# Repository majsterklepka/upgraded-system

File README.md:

# upgraded-system
Arduino Based Multi-channel Voltmeter

Arduino Design, multi-channel ADC.

- Application for OS Linux, works in terminal mode
- Sketch for Arduino UNO
- hardware project of shield for Arduino Uno

That's All! Have a fun!

## Credits

All contents on this repo is published under terms of: [CC-BY-SA](https://creativecommons.org/licenses/by-sa/4.0/) for hardware & [GNU GPLv3](https://www.gnu.org/licenses/gpl-3.0.html) for Linux software

_MSc Paweł Sobótka (SQ7EQE)_

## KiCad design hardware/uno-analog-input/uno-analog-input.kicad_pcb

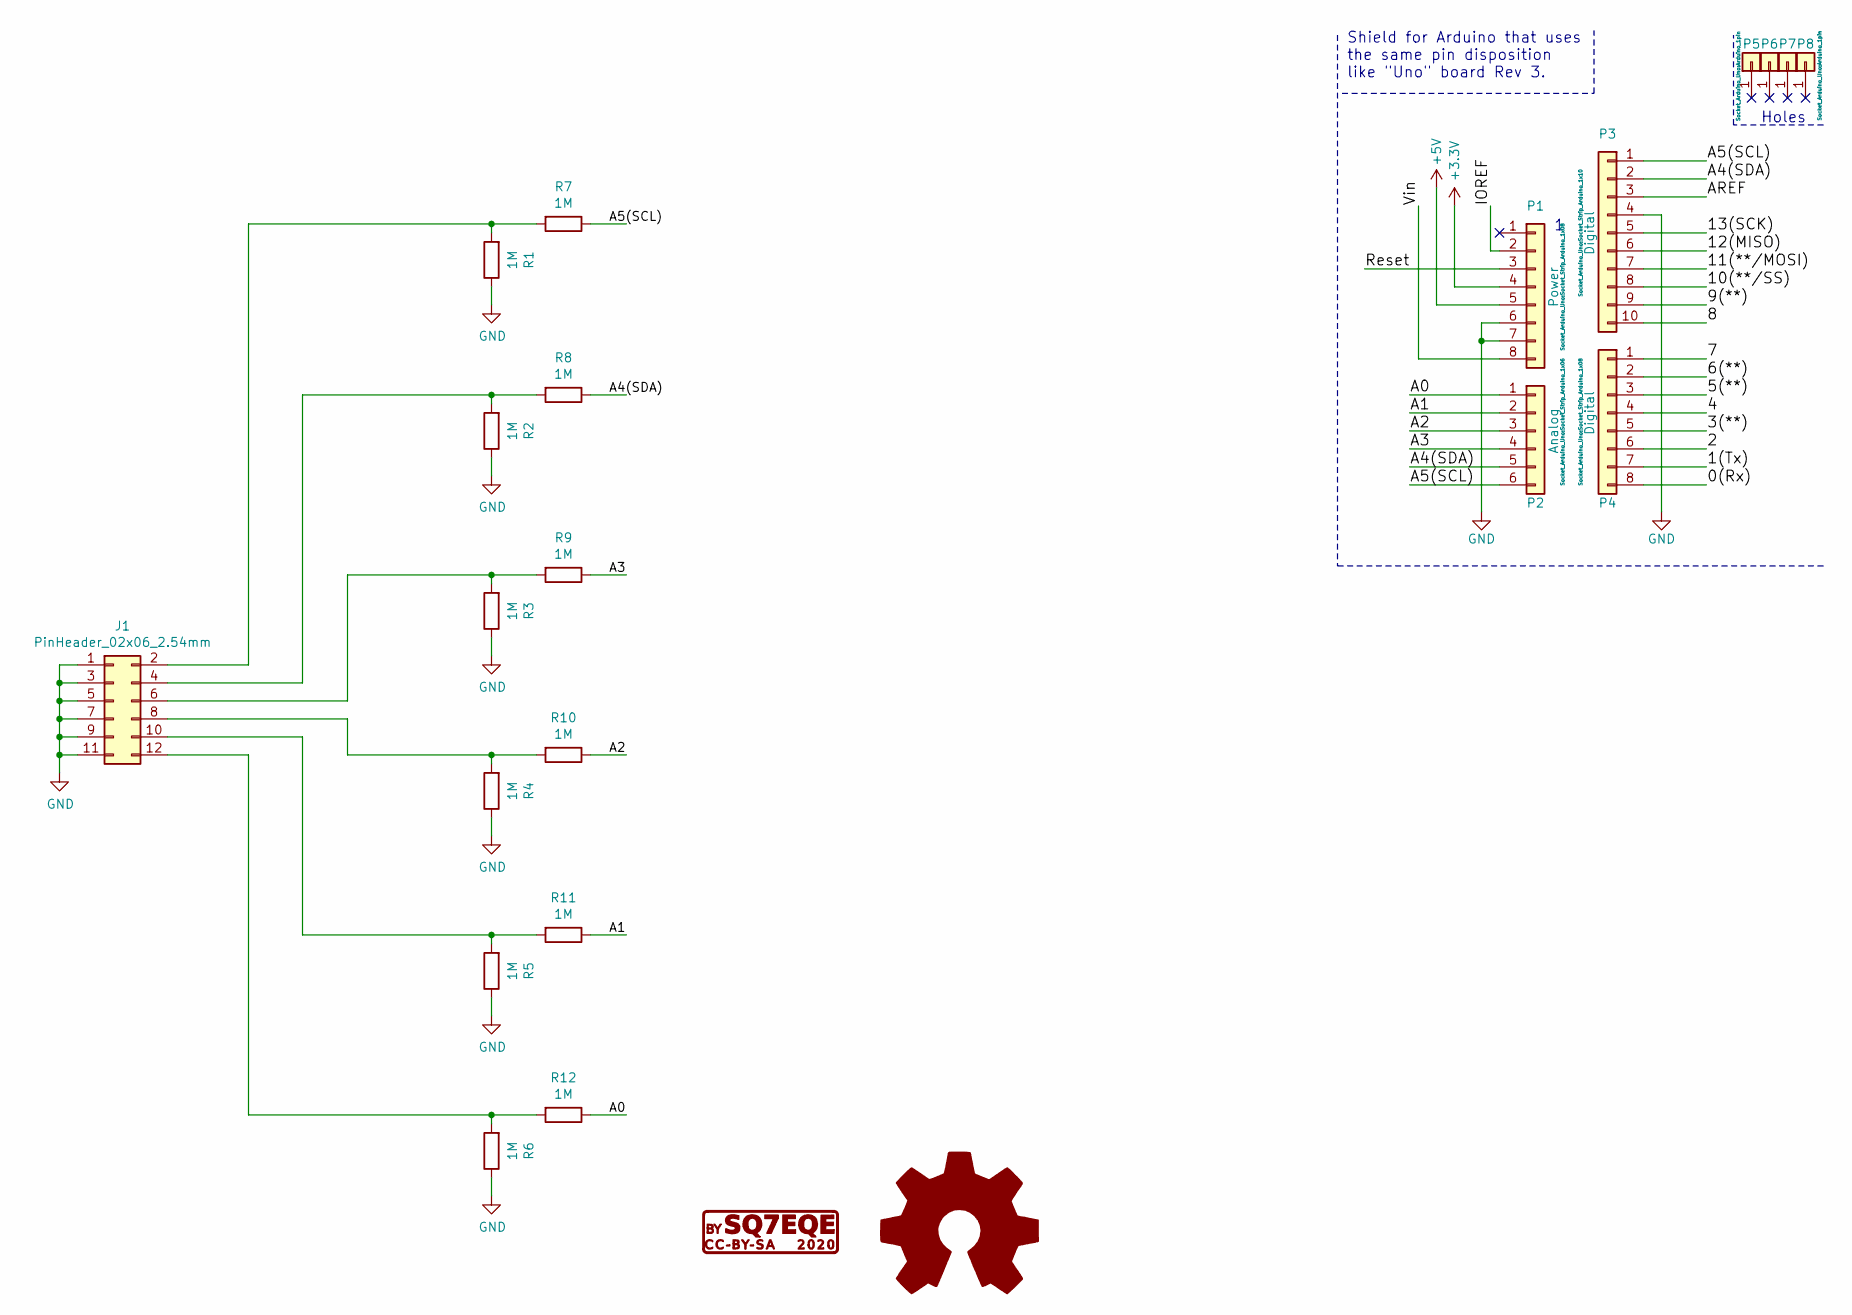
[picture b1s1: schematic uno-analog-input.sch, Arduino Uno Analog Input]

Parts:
G1: CC-BY-SA; cc-by-sa
G2: Logo_Open_Hardware_Large; OSHW-Logo2_14.6x12mm_SilkScreen
J1: PinHeader_02x06_2.54mm; PinHeader_2x06_P2.54mm_Vertical
P1: Power; Socket_Strip_Arduino_1x08
P2: Analog; Socket_Strip_Arduino_1x06
P3: Digital; Socket_Strip_Arduino_1x10
P4: Digital; Socket_Strip_Arduino_1x08
P5, P6, P7, P8: CONN_01X01; Arduino_1pin
R1, R2, R3, R4, R5, R6, R7, R8, R9, R10, R11, R12: 1M; R_Axial_DIN0204_L3.6mm_D1.6mm_P7.62mm_Horizontal

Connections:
+3V3: P1.4
+5V: P1.5
/0(Rx): P4.8
/1(Tx): P4.7
/2: P4.6
/3(**): P4.5
/4: P4.4
/5(**): P4.3
/6(**): P4.2
/7: P4.1
/8: P3.10
/9(**): P3.9
/10(**/SS): P3.8
/11(**/MOSI): P3.7
/12(MISO): P3.6
/13(SCK): P3.5
/A0: P2.1, R12.1
/A1: P2.2, R11.1
/A2: P2.3, R10.1
/A3: P2.4, R9.1
/A4(SDA): P2.5, P3.2, R8.1
/A5(SCL): P2.6, P3.1, R7.1
/AREF: P3.3
/IOREF: P1.2
/Reset: P1.3
/Vin: P1.8
GND: J1.1, J1.3, J1.5, J1.7, J1.9, J1.11, P1.6, P1.7, P3.4, R1.1, R2.1, R3.1, R4.1, R5.1, R6.1
unnamed: J1.2, R1.2, R7.2
unnamed: J1.4, R2.2, R8.2
unnamed: J1.6, R3.2, R9.2
unnamed: J1.8, R4.2, R10.2
unnamed: J1.10, R5.2, R11.2
unnamed: J1.12, R6.2, R12.2

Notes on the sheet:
Holes
Shield for Arduino that uses the same pin disposition like "Uno" board Rev 3.

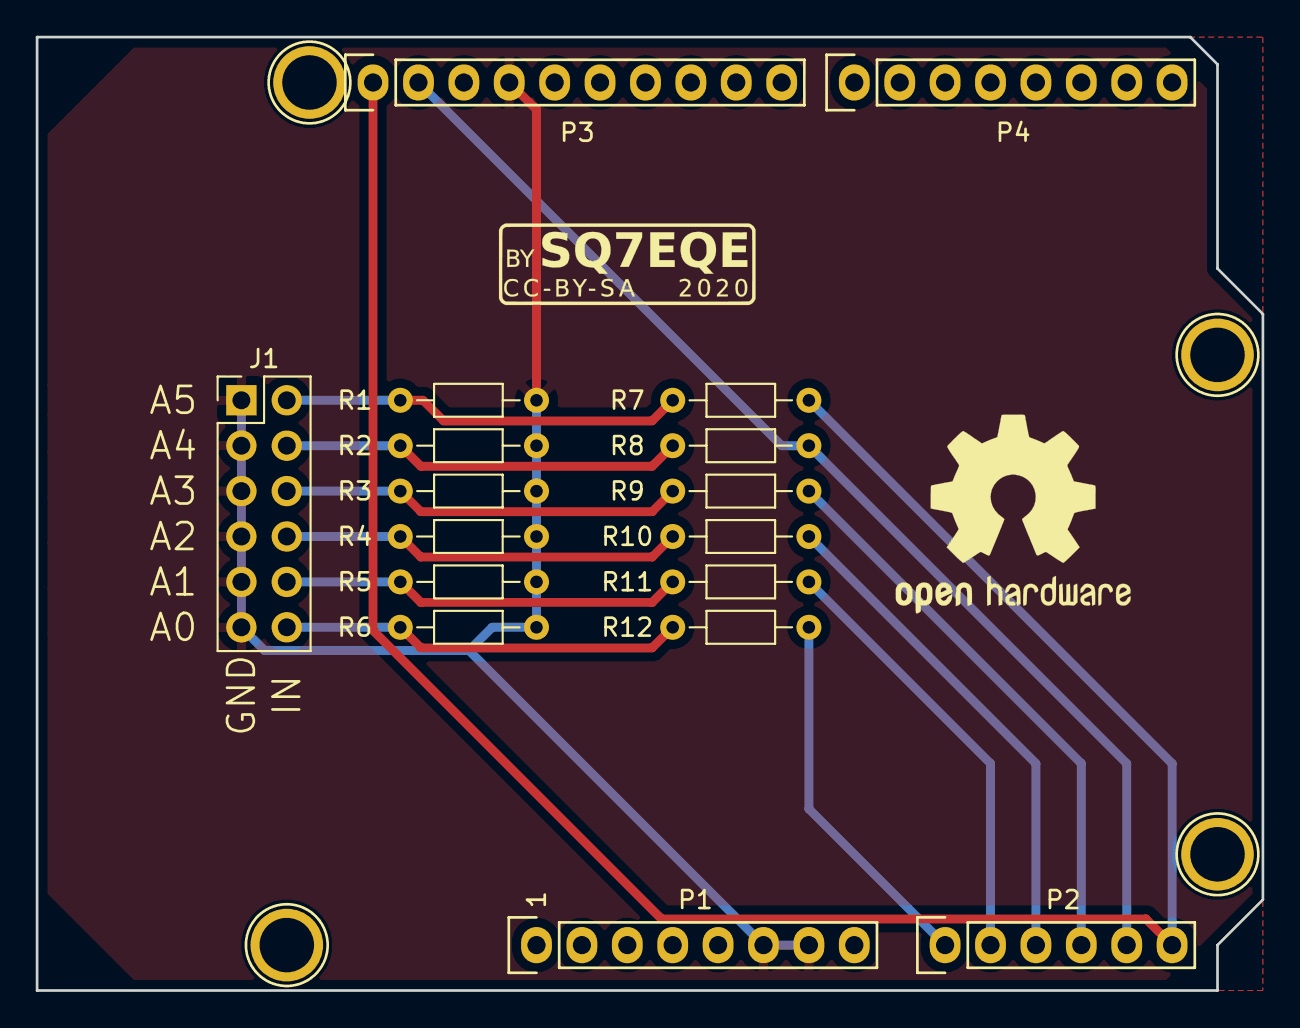
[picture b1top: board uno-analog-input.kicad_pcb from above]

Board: 2 copper layers, 68.6 x 53.3 mm, 23 parts (0 on the bottom side), 13 nets.

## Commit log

2020-06-12 upload file
2020-06-12 remove file
2020-06-12 update
    change in thread_win0() function from sleep to usleep
    faster refresh data
2020-06-12 uploaded the file
2020-06-12 update
    I have include function frozen0() which is freezing
    displayed data for 8 seconds
    functionality is calling by press key 'f' at the keyboard
    That's All! See you soon!
2020-08-09 updated file
2020-08-09 new file uploaded
    hardware project for Arduino Multi-Channel Voltmeter
    shield for Arduino Uno
2020-08-09 uploaded file
    Screenshoot with pcb design from KiCad
2020-08-10 upload modified file

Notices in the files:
hardware/uno-analog-input/uno-analog-input.kicad_pcb:
CC-BY-SA 4.0
